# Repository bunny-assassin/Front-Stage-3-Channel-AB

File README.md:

# FS-3W — Three-Way Active Front-Stage Car Amplifier

A per-side, three-channel discrete Class-AB car amplifier designed for a fully active
three-way front stage. Two identical units are built: one for the left stage, one for
the right, so left and right share no power supply, no ground return and no chassis.

**Design priority: sound quality above cost, size, efficiency and feature count.**

---

## System at a glance

| | |
|---|---|
| Units required | 2 (one per side, identical) |
| Channels per unit | 3 — tweeter, midrange, midbass |
| Loads | tweeter 4 Ω, midrange 4 Ω, midbass 2 Ω |
| Topology | discrete Class AB, three-stage, EF3 output triple, 2 output pairs/channel |
| Rails | regulated ±24 V main, regulated ±30 V front-end, regulated ±15 V line-receiver |
| Power at clipping | 62 W / 4 Ω (tweeter), 62 W / 4 Ω (mid), 113 W / 2 Ω (midbass) |
| Stability | 89° phase margin, 13 dB gain margin, worst case of every load simulated |
| Inputs | electronically balanced, 91 dB CMRR, unity gain, per-channel gain trim |
| Crossovers | none on board — external DSP does all filtering and time alignment |
| Signal path | no electrolytics, no coupling cap in the feedback loop (DC servo) |
| Supply | separate PCB, regulated push-pull SMPS, ~250 W continuous, phase-locked pair |
| Boards per unit | 2 (amplifier board + SMPS board) |

Simulated, on the netlist generated from the design source of truth: 0.0013 % THD at
1 kHz / 52 W into 4 Ω, 0.0245 % at 20 kHz, 88.7° worst-case phase margin, zero step
overshoot into any resistive load. Full tables and the caveats that go with them are in
docs/02 §2.3. Still to be confirmed at bring-up, because simulation cannot speak to
them: SNR > 110 dB A-weighted referenced to full output, damping factor > 200 at 100 Hz,
and no switching residue above −90 dBV at the speaker terminals.

## Why these numbers

You asked for "around 50 W per channel, stable to 2 Ω". A single ±24 V rail delivers
62 W on the 4 Ω channels and 113 W on the 2 Ω midbass. That asymmetry is
deliberate and free: a three-way active front stage needs the most power exactly where
the 2 Ω driver sits, and the least on the tweeter. One rail voltage therefore produces a
naturally correct power distribution without any per-channel supply complexity.

If you would rather cap the midbass nearer 50 W, drop the main rail to ±16 V and rerun
`tools/design_calcs.py`; you will lose the 4 Ω channels down to about 25 W each, which
is why the design does not do this by default.

## Read in this order

| Document | Contents |
|---|---|
| [`docs/01-system-architecture.md`](docs/01-system-architecture.md) | Block diagram, rail plan, grounding architecture, signal levels, design decision log |
| [`docs/02-amplifier-channel.md`](docs/02-amplifier-channel.md) | Channel topology, every component value, and a complete pin-to-net table |
| [`docs/03-psu-board.md`](docs/03-psu-board.md) | Push-pull converter, transformer winding spec, regulation loop, filtering |
| [`docs/04-protection-and-control.md`](docs/04-protection-and-control.md) | DC-offset, thermal, overcurrent, turn-on sequencing, muting |
| [`docs/05-pcb-layout.md`](docs/05-pcb-layout.md) | Stackup, trace sizing, net classes, grounding, placement, thermal, mechanical |
| [`docs/06-bringup-and-test.md`](docs/06-bringup-and-test.md) | Staged power-up procedure, measurements, acceptance limits |
| [`docs/07-kicad-automation.md`](docs/07-kicad-automation.md) | Toolchain and how to build the schematic and PCB programmatically |
| [`AGENT_BRIEF.md`](AGENT_BRIEF.md) | Self-contained handoff prompt for the agent that implements the PCB |
| [`bom/`](bom/) | Bill of materials per board, with alternates and sourcing notes |
| [`tools/design_calcs.py`](tools/design_calcs.py) | Every quoted number, re-derivable |

## Regenerating the design numbers

```bash
python3 tools/design_calcs.py
```

No dependencies beyond the standard library. Change an input at the top of the file
(rail voltage, load impedance, output pairs, ambient temperature) and every derived
figure — power, dissipation, heatsink requirement, compensation, transformer turns,
trace widths — is recomputed.

## Parts availability warnings

The classic parts for this kind of amplifier are dying off. Verified as of this
revision:

- **onsemi ThermalTrak (`NJL3281D`/`NJL1302D`) is discontinued.** The February 2026
  datasheet revision marks both part numbers as such. The design therefore does not
  rely on output devices with integrated bias-tracking diodes; it uses a conventional
  Vbe multiplier bolted to the heatsink instead.
- **`KSA1381`/`KSC3503` are end-of-life.** These were the standard low-Cob VAS
  transistors. Toshiba `TTA004B`/`TTC004B` are used instead, and the compensation is
  designed around their higher 12–17 pF Cob from the start. Builders report instability
  when substituting these into existing designs compensated for 2 pF parts; designing
  for them avoids that failure mode. KEC `KTC3503`/`KTA1381` are a pin- and
  spec-compatible fallback if you prefer the original characteristics.
- **`NJW0281G`/`NJW0302G` output devices are active** and gain-matched to within 10 %
  between NPN and PNP from 50 mA to 3 A, which is the single most useful property an
  output pair can have.

## Status

Design specification complete and internally consistent. Nothing has been simulated,
laid out or built yet. `docs/06-bringup-and-test.md` and `docs/07-kicad-automation.md`
define the work remaining, in order.

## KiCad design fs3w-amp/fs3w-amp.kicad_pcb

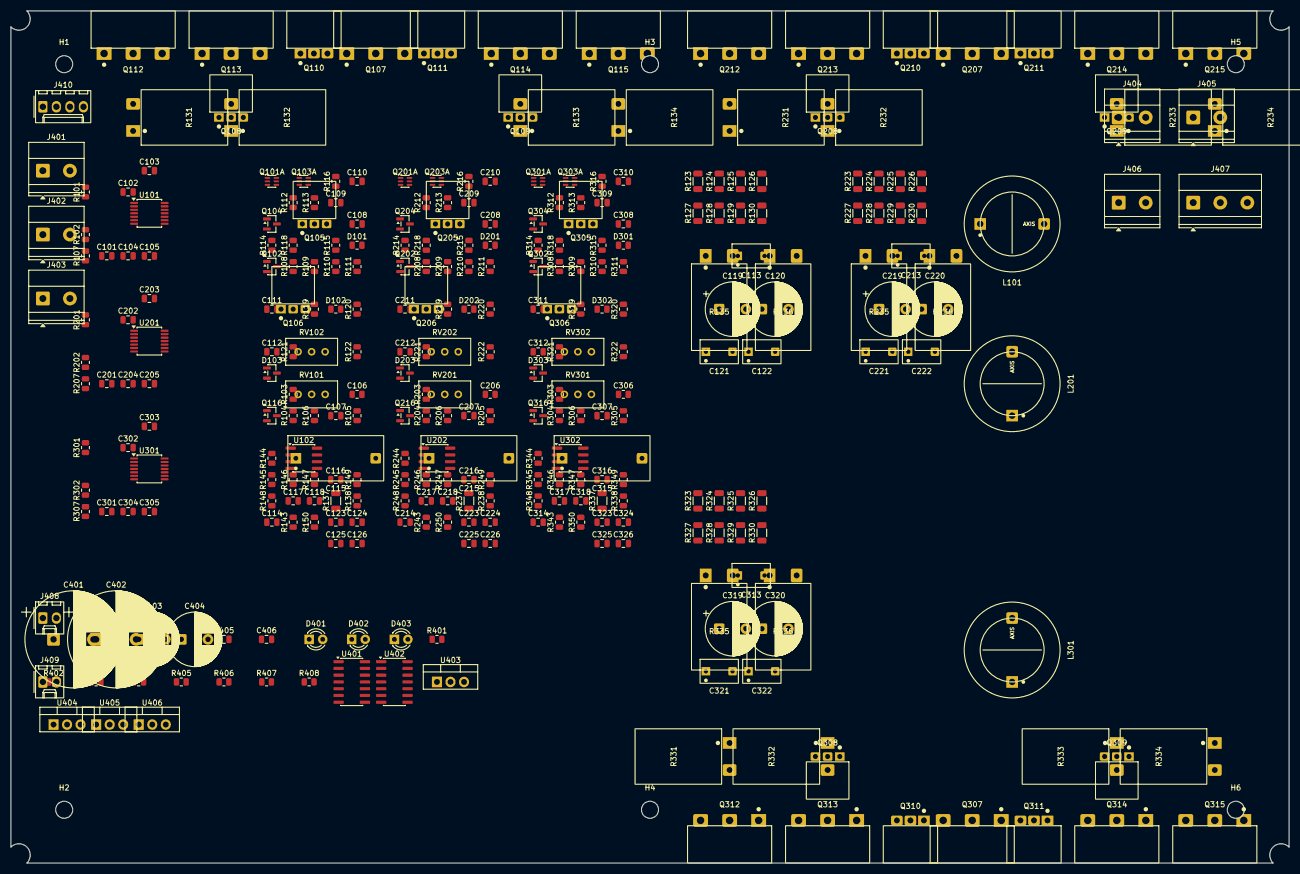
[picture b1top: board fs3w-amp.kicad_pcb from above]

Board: 4 copper layers, 240.0 x 160.0 mm, 324 parts (0 on the bottom side), 61 nets, no tracks yet.

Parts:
C101, C201, C301: 1u; C_0805_2012Metric
C102, C104, C108, C111, C112, C116, C117, C118, C125, C126, C202, C204, C208, C211, C212, C216, C217, C218, C225, C226, C302, C304, C308, C311, C312, C316, C317, C318, C325, C326: 100n; C_0805_2012Metric
C103, C105, C203, C205, C303, C305: 10u; C_0805_2012Metric
C106, C206, C306: 0R link; R_0805_2012Metric
C107, C207, C307: 220p; C_0805_2012Metric
C109, C209, C309: 68p; C_0805_2012Metric
C110, C210, C310: 1n; C_0805_2012Metric
C113, C121, C122, C213, C221, C222, C313, C321, C322: 100n/100V; C_Film_5mm_P5.00mm
C114, C214, C314: 10p; C_0805_2012Metric
C115, C215, C315: 2u2; C_Film_10mm_P15.00mm
C119, C120, C219, C220, C319, C320: 220u/35V; CP_Radial_D10.0mm_P5.00mm
C123, C124, C223, C224, C323, C324, C405, C406: 10u/50V; C_0805_2012Metric
C401, C402: 4700u/35V; CP_Radial_D18.0mm_P7.50mm
C403, C404: 220u/63V; CP_Radial_D10.0mm_P5.00mm
D101, D102, D201, D202, D301, D302: LED_RED; R_0805_2012Metric
D103, D203, D303: BZX84C5V1; SOT-23
D401: LED_GN; LED_D3.0mm
D402: LED_AM; LED_D3.0mm
D403: LED_RD; LED_D3.0mm
H1, H2, H3, H4, H5, H6: M3; MountingHole_3.2mm_M3
J401, J402, J403: TB003-500-02BE; TerminalBlock_Phoenix_MKDS-1,5-2-5.08_1x02_P5.08mm_Horizont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
J404, J405, J406: TB006-508-02BE; TerminalBlock_Phoenix_MKDS-1,5-2-5.08_1x02_P5.08mm_Horizont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
J407: TB007-762-03BE; TerminalBlock_Phoenix_MKDS-1,5-3-5.08_1x03_P5.08mm_Horizont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
J408: REMOTE; Molex_KK-254_AE-6410-02A_1x02_P2.54mm_Vertical
J409: SHUTDOWN; Molex_KK-254_AE-6410-02A_1x02_P2.54mm_Vertical
J410: AUX; Molex_KK-254_AE-6410-04A_1x04_P2.54mm_Vertical
L101, L201, L301: 2u2; L_AirCore_12mm
Q101A, Q201A, Q301A: BCM857BS; SOT-363_SC-70-6
Q102, Q202, Q302: BC857C; SOT-23
Q103A, Q203A, Q303A: BCM847BS; SOT-363_SC-70-6
Q104, Q204, Q304: BC847C; SOT-23
Q105, Q108, Q205, Q208, Q305, Q308: TTC004B; TO-126N_Vertical_HeatsinkWall
Q106, Q109, Q206, Q209, Q306, Q309: TTA004B; TO-126N_Vertical_HeatsinkWall
Q107, Q112, Q113, Q207, Q212, Q213, Q307, Q312, Q313: NJW0281G; TO-3P_Vertical_HeatsinkWall
Q110, Q210, Q310: MJE15032; TO-220-3_Vertical_HeatsinkWall
Q111, Q211, Q311: MJE15033; TO-220-3_Vertical_HeatsinkWall
Q114, Q115, Q214, Q215, Q314, Q315: NJW0302G; TO-3P_Vertical_HeatsinkWall
Q116, Q216, Q316: BSS138; SOT-23
R101, R102, R105, R115, R118, R201, R202, R205, R215, R218, R301, R302, R305, R315, R318: 100R; R_0805_2012Metric
R103, R203, R303: 2k2; R_0805_2012Metric
R104, R143, R146, R147, R204, R243, R246, R247, R304, R343, R346, R347: 100k; R_0805_2012Metric
R106, R116, R122, R145, R149, R206, R216, R222, R245, R249, R306, R316, R322, R345, R349: 1k; R_0805_2012Metric
R107, R207, R307: 1M; R_0805_2012Metric
R108, R109, R208, R209, R308, R309: 220R; R_0805_2012Metric
R110, R210, R310: 287R; R_0805_2012Metric
R111, R120, R211, R220, R311, R320: 15k; R_0805_2012Metric
R112, R113, R212, R213, R312, R313: 68R; R_0805_2012Metric
R114, R148, R150, R214, R248, R250, R314, R348, R350: 10k; R_0805_2012Metric
R119, R138, R219, R238, R319, R338: 115R; R_0805_2012Metric
R121, R221, R321: 4k42; R_0805_2012Metric
R123, R124, R137, R223, R224, R237, R323, R324, R337: 2k2; R_1206_3216Metric
R125, R126, R225, R226, R325, R326: 220R; R_1206_3216Metric
R127, R128, R129, R130, R227, R228, R229, R230, R327, R328, R329, R330: 4R7; R_1206_3216Metric
R131, R132, R133, R134, R231, R232, R233, R234, R331, R332, R333, R334: 0R22; R_TO220-2_PWR221T
R135, R136, R235, R236, R335, R336: 10R; R_TO220-2_PWR221T
R144, R244, R344: 470k; R_0805_2012Metric
R401, R403, R405, R407: 240R; R_0805_2012Metric
R402, R404: 5k62; R_0805_2012Metric
R406, R408: 2k67; R_0805_2012Metric
RV101, RV201, RV301: 10k; Potentiometer_Bourns_3296W_Vertical
RV102, RV202, RV302: 100R; Potentiometer_Bourns_3296W_Vertical
U101, U201, U301: INA1651IPW; TSSOP-14_4.4x5mm_P0.65mm
U102, U202, U302: OPA1642; SOIC-8_3.9x4.9mm_P1.27mm
U401, U402: LM339; SOIC-14_3.9x8.7mm_P1.27mm
U403, U405: LM317TG; TO-220-3_Vertical
U404, U406: LM337TG; TO-220-3_Vertical

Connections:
AIN: C106.2, C206.2, C306.2, R104.1, R105.1, R106.1, R204.1, R205.1, R206.1, R304.1, R305.1, R306.1
BADJ: Q107.1, Q207.1, Q307.1, R121.2, R221.2, R321.2, RV102.1, RV102.2, RV202.1, RV202.2, RV302.1, RV302.2
BADJ_L: R122.1, R222.1, R322.1, RV102.3, RV202.3, RV302.3
BIAS_BOT: C109.1, C112.2, C209.1, C212.2, C309.1, C312.2, D103.2, D203.2, D303.2, Q105.2, Q107.3, Q109.1, Q205.2, Q207.3, Q209.1, Q305.2, Q307.3, Q309.1, R116.1, R122.2, R216.1, R222.2, R316.1, R322.2
BIAS_TOP: C112.1, C212.1, C312.1, D103.1, D203.1, D303.1, Q106.2, Q107.2, Q108.1, Q206.2, Q207.2, Q208.1, Q306.2, Q307.2, Q308.1, R121.1, R221.1, R321.1
CSREF: C111.1, C211.1, C311.1, D102.1, D202.1, D302.1, Q106.1, Q206.1, Q306.1, R120.1, R220.1, R320.1
DR_N: Q110.3, Q210.3, Q310.3, R125.1, R127.1, R128.1, R225.1, R227.1, R228.1, R325.1, R327.1, R328.1
DR_P: Q111.3, Q211.3, Q311.3, R126.1, R129.1, R130.1, R226.1, R229.1, R230.1, R326.1, R329.1, R330.1
FB: C114.2, C214.2, C314.2, R137.2, R138.1, R148.2, R237.2, R238.1, R248.2, R337.2, R338.1, R348.2
LC_A: C109.2, C110.2, C209.2, C210.2, C309.2, C310.2, Q101A.2, Q103A.2, Q104.1, Q201A.2, Q203A.2, Q204.1, Q301A.2, Q303A.2, Q304.1
LC_B: Q103A.1, Q203A.1, Q303A.1
LTP_INP: C107.1, C207.1, C307.1, Q101A.1, Q201A.1, Q301A.1, R106.2, R206.2, R306.2
MUTE_CTL: Q116.1, Q216.1, Q316.1
MUTE_NODE: Q116.2, Q216.2, Q316.2, R105.2, R205.2, R305.2
OUT_STAR: C114.1, C214.1, C314.1, L101.1, L201.1, L301.1, R123.2, R124.2, R125.2, R126.2, R131.2, R132.2, R133.2, R134.2, R135.1, R136.1, R137.1, R143.1, R144.1, R223.2, R224.2, R225.2, R226.2, R231.2, R232.2, R233.2, R234.2, R235.1, R236.1, R237.1, R243.1, R244.1, R323.2, R324.2, R325.2, R326.2, R331.2, R332.2, R333.2, R334.2, R335.1, R336.1, R337.1, R343.1, R344.1
PD_N: Q108.3, Q110.1, Q208.3, Q210.1, Q308.3, Q310.1, R123.1, R223.1, R323.1
PD_P: Q109.3, Q111.1, Q209.3, Q211.1, Q309.3, Q311.1, R124.1, R224.1, R324.1
PWR_GND: C113.2, C119.2, C120.1, C121.2, C122.2, C213.2, C219.2, C220.1, C221.2, C222.2, C313.2, C319.2, C320.1, C321.2, C322.2
Q1A_E: Q101A.3, Q201A.3, Q301A.3, R108.1, R208.1, R308.1
Q1B_E: R109.1, R209.1, R309.1
Q2_E: Q102.3, Q202.3, Q302.3, R110.2, R210.2, R310.2
Q3A_E: Q103A.3, Q203A.3, Q303A.3, R112.1, R212.1, R312.1
Q3B_E: R113.1, R213.1, R313.1
Q5_B: Q105.1, Q205.1, Q305.1, R118.2, R218.2, R318.2
Q5_E: Q105.3, Q205.3, Q305.3, R115.1, R215.1, R315.1
Q6_E: Q106.3, Q206.3, Q306.3, R119.2, R219.2, R319.2
Q12_B: Q112.1, Q212.1, Q312.1, R127.2, R227.2, R327.2
Q12_E: Q112.3, Q212.3, Q312.3, R131.1, R150.1, R231.1, R250.1, R331.1, R350.1
Q13_B: Q113.1, Q213.1, Q313.1, R128.2, R228.2, R328.2
Q13_E: Q113.3, Q213.3, Q313.3, R132.1, R232.1, R332.1
Q14_B: Q114.1, Q214.1, Q314.1, R129.2, R229.2, R329.2
Q14_E: Q114.3, Q214.3, Q314.3, R133.1, R233.1, R333.1
Q15_B: Q115.1, Q215.1, Q315.1, R130.2, R230.2, R330.2
Q15_E: Q115.3, Q215.3, Q315.3, R134.1, R234.1, R334.1
RX: R103.1, R203.1, R303.1, U101.13, U201.13, U301.13
RX_INN: R102.2, R202.2, R302.2, U101.4, U201.4, U301.4
RX_INP: R101.2, R201.2, R301.2, U101.2, U201.2, U301.2
SIG_GND: C101.2, C102.2, C103.2, C104.2, C105.2, C107.2, C117.2, C118.2, C123.2, C124.2, C125.2, C126.2, C201.2, C202.2, C203.2, C204.2, C205.2, C207.2, C217.2, C218.2, C223.2, C224.2, C225.2, C226.2, C301.2, C302.2, C303.2, C304.2, C305.2, C307.2, C317.2, C318.2, C323.2, C324.2, C325.2, C326.2, Q116.3, Q216.3, Q316.3, R104.2, R107.1, R107.2, R111.2, R120.2, R138.2, R145.2, R149.2, R204.2, R207.1, R207.2, R211.2, R220.2, R238.2, R245.2, R249.2, R304.2, R307.1, R307.2, R311.2, R320.2, R338.2, R345.2, R349.2, RV101.3, RV201.3, RV301.3, U101.3, U101.12, U201.3, U201.12, U301.3, U301.12
SPK_B: L301.2, R336.2
SPK_M: L201.2, R236.2
SPK_T: L101.2, R136.2
SRV_A_IN: C115.1, C215.1, C315.1, R144.2, R244.2, R344.2, U102.2, U202.2, U302.2
SRV_A_OUT: C115.2, C215.2, C315.2, R146.1, R246.1, R346.1, U102.1, U202.1, U302.1
SRV_A_REF: R145.1, R245.1, R345.1, U102.3, U202.3, U302.3
SRV_B_IN: C116.1, C216.1, C316.1, R146.2, R147.1, R246.2, R247.1, R346.2, R347.1, U102.6, U202.6, U302.6
SRV_B_OUT: C116.2, C216.2, C316.2, R147.2, R148.1, R247.2, R248.1, R347.2, R348.1, U102.7, U202.7, U302.7
SRV_B_REF: R149.1, R249.1, R349.1, U102.5, U202.5, U302.5
TAIL: Q102.2, Q202.2, Q302.2, R108.2, R109.2, R208.2, R209.2, R308.2, R309.2
TP_NODE: C110.1, C210.1, C310.1, R116.2, R216.2, R316.2
TREF: C108.1, C208.1, C308.1, D101.1, D201.1, D301.1, Q102.1, Q202.1, Q302.1, R111.1, R211.1, R311.1
TRIM: C106.1, C206.1, C306.1, RV101.2, RV201.2, RV301.2
TRIM_TOP: R103.2, R203.2, R303.2, RV101.1, RV201.1, RV301.1
VB_PRE: Q104.3, Q204.3, Q304.3, R114.1, R118.1, R214.1, R218.1, R314.1, R318.1
VCC_15: C102.1, C103.1, C117.1, C202.1, C203.1, C217.1, C302.1, C303.1, C317.1, U101.1, U102.8, U201.1, U202.8, U301.1, U302.8
VCC_FE: C108.2, C111.2, C123.1, C125.1, C208.2, C211.2, C223.1, C225.1, C308.2, C311.2, C323.1, C325.1, D101.2, D102.2, D201.2, D202.2, D301.2, D302.2, Q104.2, Q108.2, Q204.2, Q208.2, Q304.2, Q308.2, R110.1, R119.1, R210.1, R219.1, R310.1, R319.1
VCC_MAIN: C119.1, C121.1, C219.1, C221.1, C319.1, C321.1, Q110.2, Q112.2, Q113.2, Q210.2, Q212.2, Q213.2, Q310.2, Q312.2, Q313.2
VEE_15: C104.1, C105.1, C118.1, C204.1, C205.1, C218.1, C304.1, C305.1, C318.1, U101.14, U102.4, U201.14, U202.4, U301.14, U302.4
VEE_FE: C124.1, C126.1, C224.1, C226.1, C324.1, C326.1, Q109.2, Q209.2, Q309.2, R112.2, R113.2, R114.2, R115.2, R212.2, R213.2, R214.2, R215.2, R312.2, R313.2, R314.2, R315.2
VEE_MAIN: C120.2, C122.1, C220.2, C222.1, C320.2, C322.1, Q111.2, Q114.2, Q115.2, Q211.2, Q214.2, Q215.2, Q311.2, Q314.2, Q315.2
VMID: C101.1, C201.1, C301.1, U101.11, U201.11, U301.11
ZOB: C113.1, C213.1, C313.1, R135.2, R235.2, R335.2
